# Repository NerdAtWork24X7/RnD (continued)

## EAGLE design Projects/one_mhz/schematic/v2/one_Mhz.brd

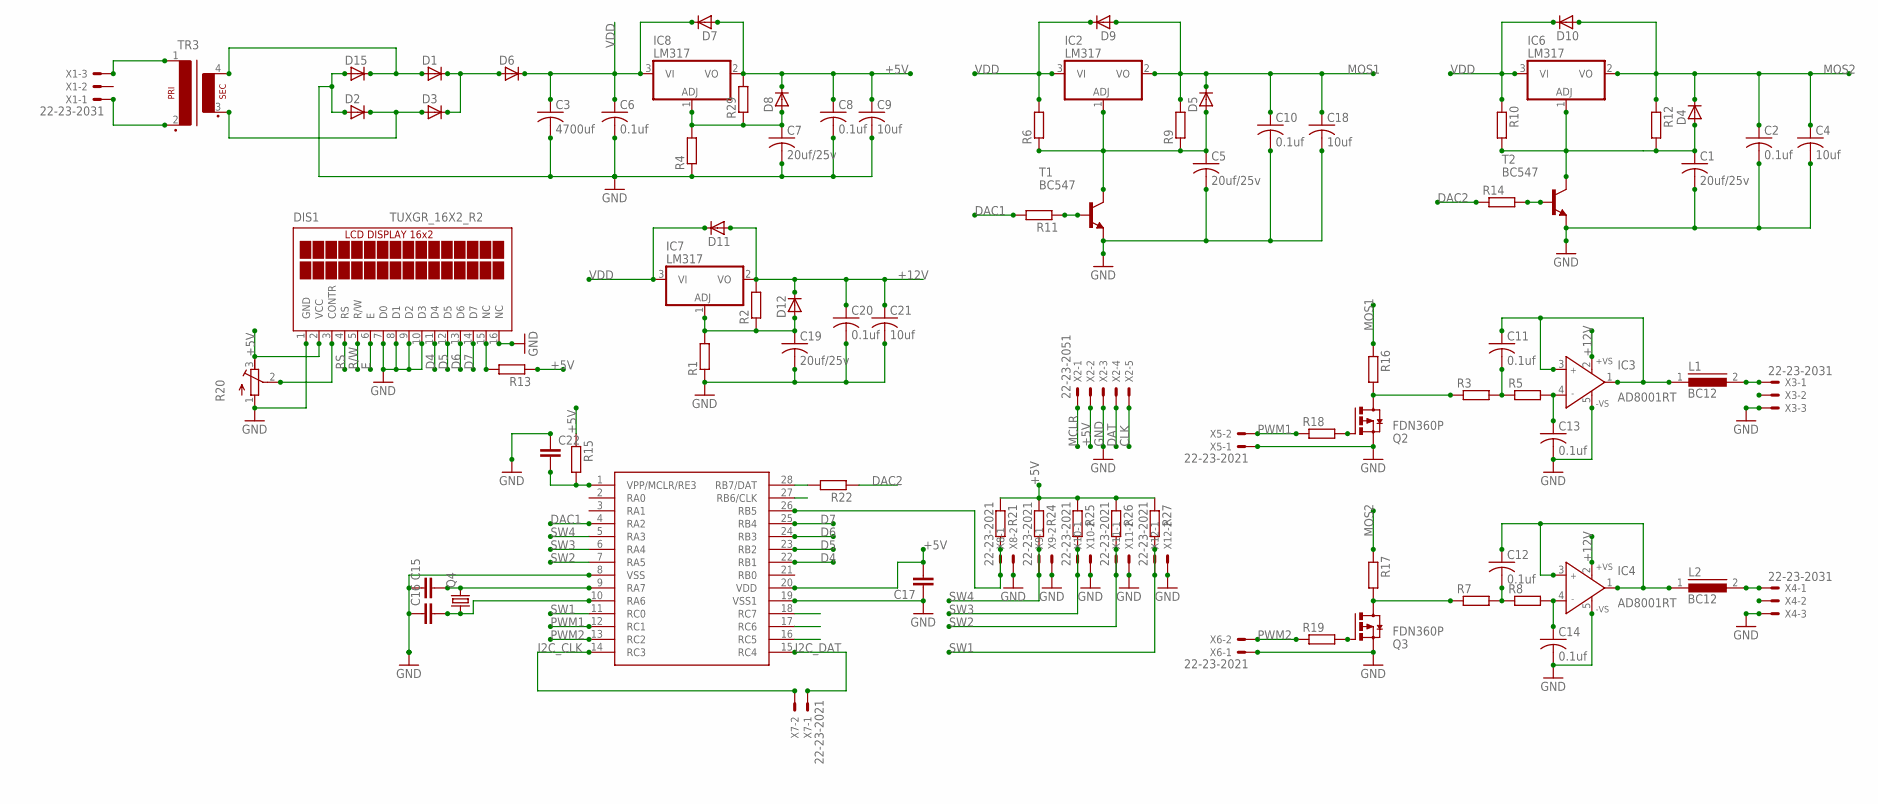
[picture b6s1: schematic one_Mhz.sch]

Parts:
C1, C5, C7, C19: 20uf/25v; C025-025X050
C2, C6, C8, C10, C11, C12, C13, C14, C20: 0.1uf; C025-025X050
C3: 4700uf; C025-025X050
C4, C9, C18, C21: 10uf; C025-025X050
C15, C16, C17, C22: CC0603; C0603
D1, D2, D3, D4, D5, D6, D7, D8, D9, D10, D11, D12, D15: D-SOD-87; SOD87
DIS1: TUXGR_16X2_R2
IC2, IC6, IC8: LM317; TO92
IC3, IC4: AD8001RT; SOT23-5
IC7: LM317; TO220H
L1, L2: BC12
Q2, Q3: FDN360P; SUPER-SOT3
Q4: CRYSTALHC49U-V; HC49U-V
R1, R2, R3, R4, R5, R6, R7, R8, R9, R10, R11, R12, R13, R14, R15, R16, R17, R18, R19, R21, R22, R24, R25, R26, R27, R29: R-EU_R0603; R0603
R20: R-TRIMM64X; RTRIM64X
T1, T2: BC547; TO92
TR3: VR13-1
U$1: PIC16F15345; SO28W
X1, X3, X4: 22-23-2031
X2: 22-23-2051
X5, X6, X7, X8, X9, X10, X11, X12: 22-23-2021

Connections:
+5V: C8.1, C9.1, C17.2, D7.2 (A), D8.1 (C), DIS1.2 (VCC), IC8.2 (VO), R13.1, R15.1, R20.3 (E), R21.1, R24.1, R25.1, R26.1, R27.1, R29.2, U$1.20 (VDD), X2.2
+12V: C20.1, C21.1, D11.2 (A), D12.1 (C), IC3.2 (+VS), IC4.2 (+VS), IC7.2 (VO), R2.2
CLK: U$1.27 (RB6/CLK), X2.5
D4: DIS1.11 (D4), U$1.22 (RB1)
D5: DIS1.12 (D5), U$1.23 (RB2)
D6: DIS1.13 (D6), U$1.24 (RB3)
D7: DIS1.14 (D7), U$1.25 (RB4)
DAC1: R11.2, U$1.4 (RA2)
DAC2: R14.1, R22.1
DAT: R22.2, U$1.28 (RB7/DAT), X2.4
E: DIS1.6 (E), U$1.18 (RC7)
GND: C1.2, C2.2, C3.2, C4.2, C5.2, C6.2, C7.2, C8.2, C9.2, C10.2, C13.2, C14.2, C15.1, C16.1, C17.1, C18.2, C19.2, C20.2, C21.2, C22.1, D2.2 (A), D15.2 (A), DIS1.1 (GND), DIS1.7 (D0), DIS1.8 (D1), DIS1.9 (D2), DIS1.10 (D3), DIS1.16 (NC), IC3.5 (-VS), IC4.5 (-VS), Q2.2 (S), Q3.2 (S), R1.1, R4.1, R20.1 (A), T1.1 (E), T2.1 (E), U$1.8 (VSS), U$1.19 (VSS1), X2.3, X3.3, X4.3, X5.1, X6.1, X8.2, X9.2, X10.2, X11.2, X12.2
I2C_CLK: U$1.14 (RC3), X7.2
I2C_DAT: U$1.15 (RC4), X7.1
MCLR: C22.2, R15.2, U$1.1 (VPP/MCLR/RE3), X2.1
MOS1: C10.1, C18.1, D5.1 (C), D9.2 (A), IC2.2 (VO), R9.2, R16.1
MOS2: C2.1, C4.1, D4.1 (C), D10.2 (A), IC6.2 (VO), R12.1, R17.1
unnamed: L2.2, X4.1
unnamed: D1.1 (C), D3.1 (C), D6.2 (A)
unnamed: D1.2 (A), D15.1 (C), TR3.4 (S4)
unnamed: D2.1 (C), D3.2 (A), TR3.3 (S3)
unnamed: Q3.3 (D), R7.1, R17.2
unnamed: C13.1, IC3.4 (IN-), R5.2
unnamed: DIS1.15 (NC), R13.2
unnamed: Q2.3 (D), R3.1, R16.2
unnamed: C7.1, D8.2 (A), IC8.1 (ADJ), R4.2, R29.1
unnamed: R21.2, U$1.26 (RB5), X8.1
unnamed: C14.1, IC4.4 (IN-), R8.2
unnamed: C12.2, R7.2, R8.1
unnamed: C11.2, R3.2, R5.1
unnamed: C11.1, IC3.1 (OUT), IC3.3 (IN+), L1.1
unnamed: C12.1, IC4.1 (OUT), IC4.3 (IN+), L2.1
unnamed: DIS1.3 (CONTR), R20.2 (S)
unnamed: Q2.1 (G), R18.2
unnamed: Q3.1 (G), R19.2
unnamed: C5.1, D5.2 (A), IC2.1 (ADJ), R6.1, R9.1, T1.3 (C)
unnamed: C1.1, D4.2 (A), IC6.1 (ADJ), R10.2, R12.2, T2.3 (C)
unnamed: R11.1, T1.2 (B)
unnamed: R14.2, T2.2 (B)
unnamed: C19.1, D12.2 (A), IC7.1 (ADJ), R1.2, R2.1
unnamed: L1.2, X3.1
unnamed: TR3.1, X1.3
unnamed: TR3.2, X1.1
unnamed: C16.2, Q4.1, U$1.10 (RA6)
unnamed: C15.2, Q4.2, U$1.9 (RA7)
PWM1: R18.1, U$1.12 (RC1), X5.2
PWM2: R19.1, U$1.13 (RC2), X6.2
R/W: DIS1.5 (R/W), U$1.17 (RC6)
RS: DIS1.4 (RS), U$1.16 (RC5)
SW1: R27.2, U$1.11 (RC0), X12.1
SW2: R26.2, U$1.7 (RA5), X11.1
SW3: R25.2, U$1.6 (RA4), X10.1
SW4: R24.2, U$1.5 (RA3), X9.1
VDD: C3.1, C6.1, D6.1 (C), D7.1 (C), D9.1 (C), D10.1 (C), D11.1 (C), IC2.3 (VI), IC6.3 (VI), IC7.3 (VI), IC8.3 (VI), R6.2, R10.1

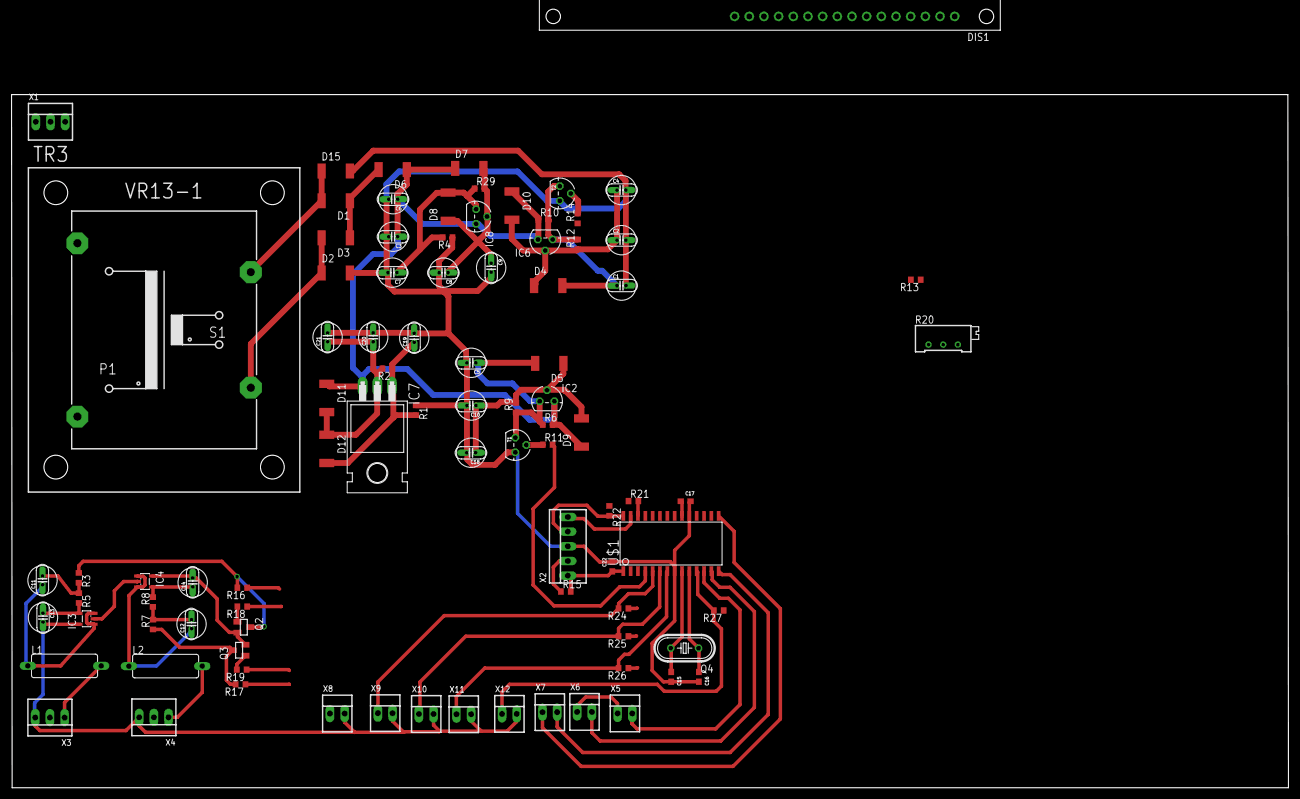
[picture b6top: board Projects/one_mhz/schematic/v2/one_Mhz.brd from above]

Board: 2 copper layers, 221.1 x 120.0 mm, 90 parts (0 on the bottom side), 54 nets.
